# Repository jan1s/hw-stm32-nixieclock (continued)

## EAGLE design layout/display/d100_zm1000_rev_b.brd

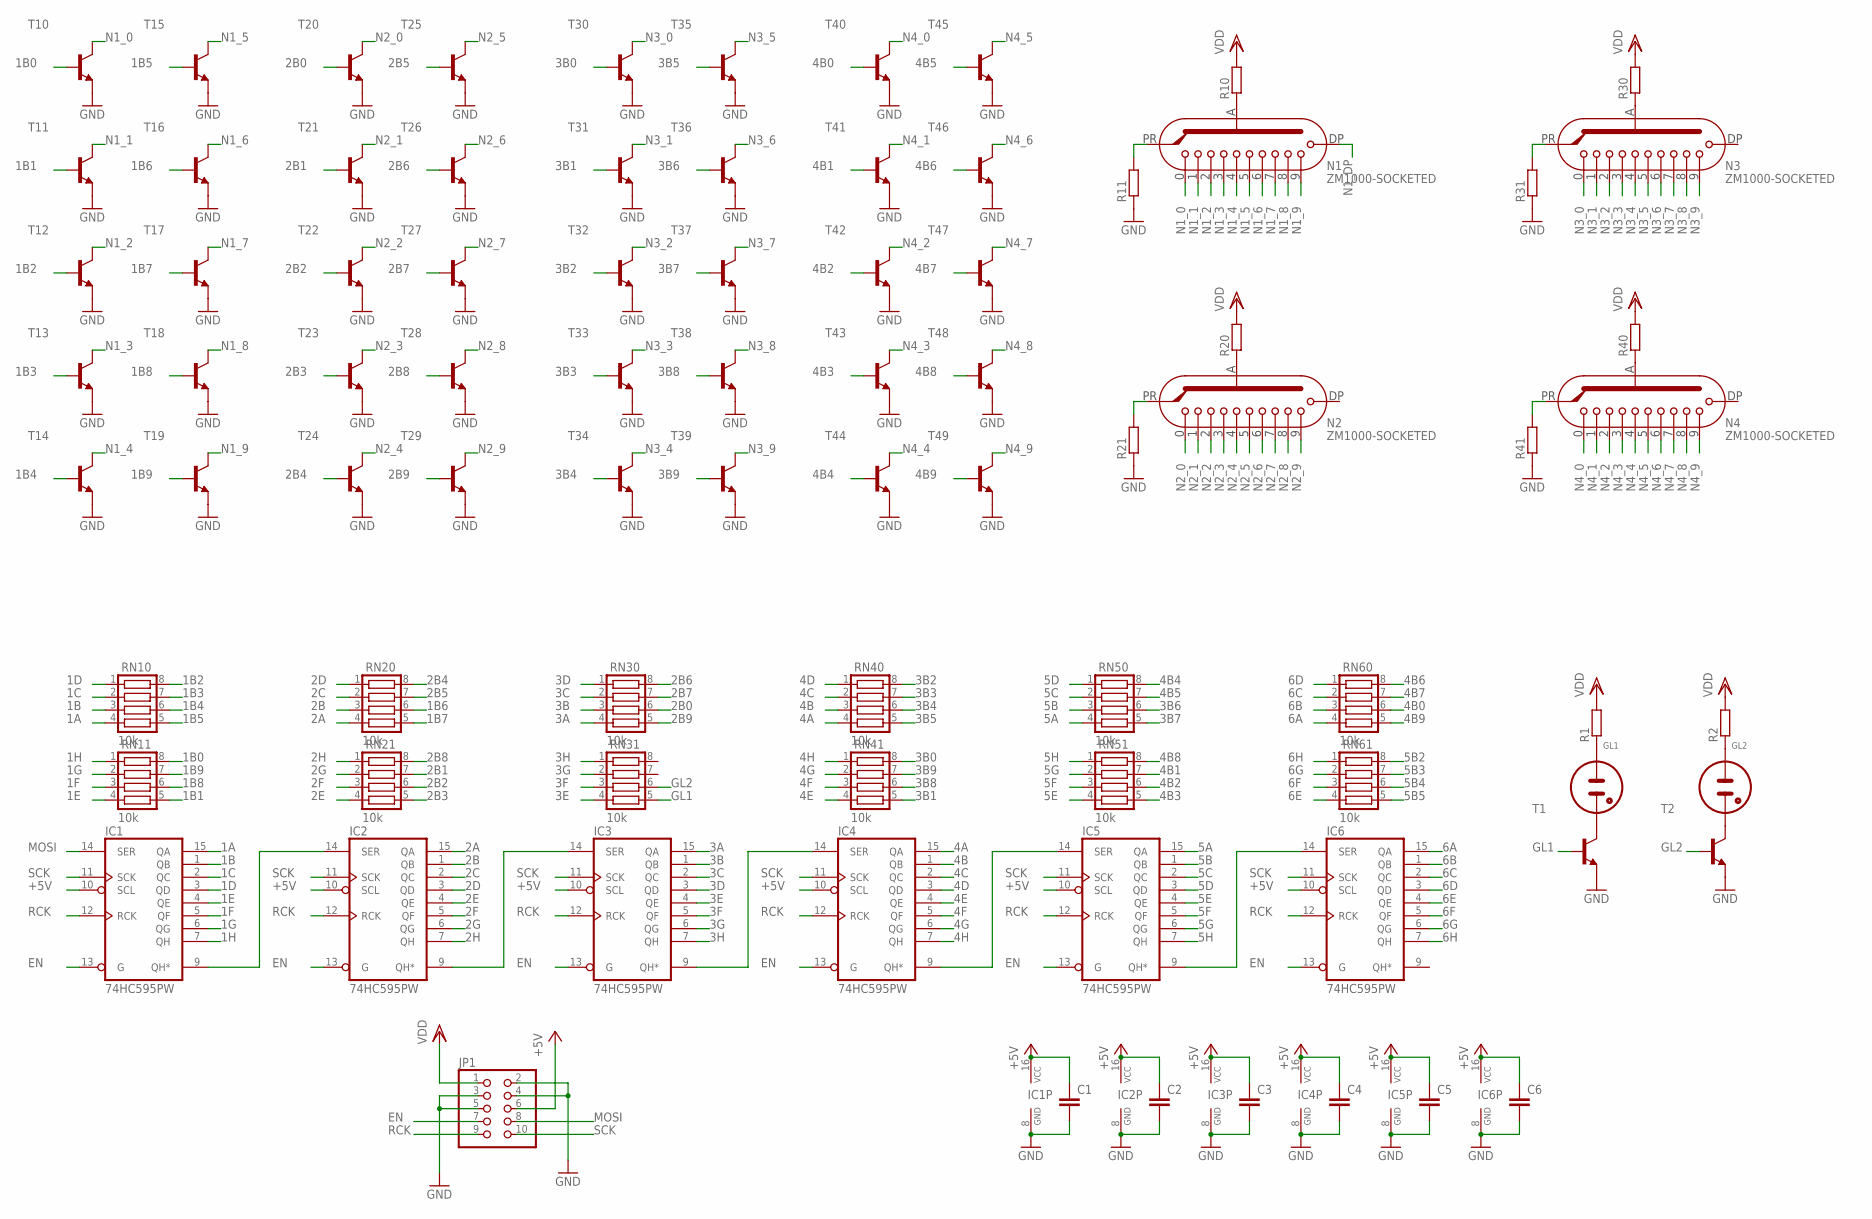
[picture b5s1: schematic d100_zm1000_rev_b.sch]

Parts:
C1, C2, C3, C4, C5, C6: C-EUC0603; C0603
GL1, GL2: NE2-NEON-BULB-DRILL
IC1, IC2, IC3, IC4, IC5, IC6: 74HC595PW; TSSOP16
JP1: PINHD-2X5_2.54-SMD; 2X05SMD
N1, N2, N3, N4: ZM1000-SOCKETED
R1, R2, R10, R11, R20, R21, R30, R31, R40, R41: R-EU_R0603; R0603
RN10, RN11, RN20, RN21, RN30, RN31, RN40, RN41, RN50, RN51, RN60, RN61: 10k; CTS742C083
T1, T2, T10, T11, T12, T13, T14, T15, T16, T17, T18, T19, T20, T21, T22, T23, T24, T25, T26, T27, T28, T29, T30, T31, T32, T33, T34, T35, T36, T37, T38, T39, T40, T41, T42, T43, T44, T45, T46, T47, T48, T49: SMBTA42; SOT23

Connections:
1A: IC1.15 (QA), RN10.4
1B: IC1.1 (QB), RN10.3
1B0: RN11.8, T10.1 (B)
1B1: RN11.5, T11.1 (B)
1B2: RN10.8, T12.1 (B)
1B3: RN10.7, T13.1 (B)
1B4: RN10.6, T14.1 (B)
1B5: RN10.5, T15.1 (B)
1B6: RN20.6, T16.1 (B)
1B7: RN20.5, T17.1 (B)
1B8: RN11.6, T18.1 (B)
1B9: RN11.7, T19.1 (B)
1C: IC1.2 (QC), RN10.2
1D: IC1.3 (QD), RN10.1
1E: IC1.4 (QE), RN11.4
1F: IC1.5 (QF), RN11.3
1G: IC1.6 (QG), RN11.2
1H: IC1.7 (QH), RN11.1
2A: IC2.15 (QA), RN20.4
2B: IC2.1 (QB), RN20.3
2B0: RN30.6, T20.1 (B)
2B1: RN21.7, T21.1 (B)
2B2: RN21.6, T22.1 (B)
2B3: RN21.5, T23.1 (B)
2B4: RN20.8, T24.1 (B)
2B5: RN20.7, T25.1 (B)
2B6: RN30.8, T26.1 (B)
2B7: RN30.7, T27.1 (B)
2B8: RN21.8, T28.1 (B)
2B9: RN30.5, T29.1 (B)
2C: IC2.2 (QC), RN20.2
2D: IC2.3 (QD), RN20.1
2E: IC2.4 (QE), RN21.4
2F: IC2.5 (QF), RN21.3
2G: IC2.6 (QG), RN21.2
2H: IC2.7 (QH), RN21.1
3A: IC3.15 (QA), RN30.4
3B: IC3.1 (QB), RN30.3
3B0: RN41.8, T30.1 (B)
3B1: RN41.5, T31.1 (B)
3B2: RN40.8, T32.1 (B)
3B3: RN40.7, T33.1 (B)
3B4: RN40.6, T34.1 (B)
3B5: RN40.5, T35.1 (B)
3B6: RN50.6, T36.1 (B)
3B7: RN50.5, T37.1 (B)
3B8: RN41.6, T38.1 (B)
3B9: RN41.7, T39.1 (B)
3C: IC3.2 (QC), RN30.2
3D: IC3.3 (QD), RN30.1
3E: IC3.4 (QE), RN31.4
3F: IC3.5 (QF), RN31.3
3G: IC3.6 (QG), RN31.2
3H: IC3.7 (QH), RN31.1
4A: IC4.15 (QA), RN40.4
4B: IC4.1 (QB), RN40.3
4B0: RN60.6, T40.1 (B)
4B1: RN51.7, T41.1 (B)
4B2: RN51.6, T42.1 (B)
4B3: RN51.5, T43.1 (B)
4B4: RN50.8, T44.1 (B)
4B5: RN50.7, T45.1 (B)
4B6: RN60.8, T46.1 (B)
4B7: RN60.7, T47.1 (B)
4B8: RN51.8, T48.1 (B)
4B9: RN60.5, T49.1 (B)
4C: IC4.2 (QC), RN40.2
4D: IC4.3 (QD), RN40.1
4E: IC4.4 (QE), RN41.4
4F: IC4.5 (QF), RN41.3
4G: IC4.6 (QG), RN41.2
4H: IC4.7 (QH), RN41.1
5A: IC5.15 (QA), RN50.4
5B: IC5.1 (QB), RN50.3
5B2: RN61.8
5B3: RN61.7
5B4: RN61.6
5B5: RN61.5
5C: IC5.2 (QC), RN50.2
5D: IC5.3 (QD), RN50.1
5E: IC5.4 (QE), RN51.4
5F: IC5.5 (QF), RN51.3
5G: IC5.6 (QG), RN51.2
5H: IC5.7 (QH), RN51.1
6A: IC6.15 (QA), RN60.4
6B: IC6.1 (QB), RN60.3
6C: IC6.2 (QC), RN60.2
6D: IC6.3 (QD), RN60.1
6E: IC6.4 (QE), RN61.4
6F: IC6.5 (QF), RN61.3
6G: IC6.6 (QG), RN61.2
6H: IC6.7 (QH), RN61.1
+5V: C1.1, C2.1, C3.1, C4.1, C5.1, C6.1, IC1.10 (SCL), IC1.16 (VCC), IC2.10 (SCL), IC2.16 (VCC), IC3.10 (SCL), IC3.16 (VCC), IC4.10 (SCL), IC4.16 (VCC), IC5.10 (SCL), IC5.16 (VCC), IC6.10 (SCL), IC6.16 (VCC), JP1.6
EN: IC1.13 (G), IC2.13 (G), IC3.13 (G), IC4.13 (G), IC5.13 (G), IC6.13 (G), JP1.7
GL1: RN31.5, T1.1 (B)
GL2: RN31.6, T2.1 (B)
GND: C1.2, C2.2, C3.2, C4.2, C5.2, C6.2, IC1.8 (GND), IC2.8 (GND), IC3.8 (GND), IC4.8 (GND), IC5.8 (GND), IC6.8 (GND), JP1.2, JP1.3, JP1.4, JP1.5, R11.1, R21.1, R31.1, R41.1, T1.2 (E), T2.2 (E), T10.2 (E), T11.2 (E), T12.2 (E), T13.2 (E), T14.2 (E), T15.2 (E), T16.2 (E), T17.2 (E), T18.2 (E), T19.2 (E), T20.2 (E), T21.2 (E), T22.2 (E), T23.2 (E), T24.2 (E), T25.2 (E), T26.2 (E), T27.2 (E), T28.2 (E), T29.2 (E), T30.2 (E), T31.2 (E), T32.2 (E), T33.2 (E), T34.2 (E), T35.2 (E), T36.2 (E), T37.2 (E), T38.2 (E), T39.2 (E), T40.2 (E), T41.2 (E), T42.2 (E), T43.2 (E), T44.2 (E), T45.2 (E), T46.2 (E), T47.2 (E), T48.2 (E), T49.2 (E)
MOSI: IC1.14 (SER), JP1.8
N1_0: N1.K0 (0), T10.3 (C)
N1_1: N1.K1 (1), T11.3 (C)
N1_2: N1.K2 (2), T12.3 (C)
N1_3: N1.K3 (3), T13.3 (C)
N1_4: N1.K4 (4), T14.3 (C)
N1_5: N1.K5 (5), T15.3 (C)
N1_6: N1.K6 (6), T16.3 (C)
N1_7: N1.K7 (7), T17.3 (C)
N1_8: N1.K8 (8), T18.3 (C)
N1_9: N1.K9 (9), T19.3 (C)
N1_DP: N1.KDP (DP)
N1_PR: N1.PR, R11.2
N2_0: N2.K0 (0), T20.3 (C)
N2_1: N2.K1 (1), T21.3 (C)
N2_2: N2.K2 (2), T22.3 (C)
N2_3: N2.K3 (3), T23.3 (C)
N2_4: N2.K4 (4), T24.3 (C)
N2_5: N2.K5 (5), T25.3 (C)
N2_6: N2.K6 (6), T26.3 (C)
N2_7: N2.K7 (7), T27.3 (C)
N2_8: N2.K8 (8), T28.3 (C)
N2_9: N2.K9 (9), T29.3 (C)
N3_0: N3.K0 (0), T30.3 (C)
N3_1: N3.K1 (1), T31.3 (C)
N3_2: N3.K2 (2), T32.3 (C)
N3_3: N3.K3 (3), T33.3 (C)
N3_4: N3.K4 (4), T34.3 (C)
N3_5: N3.K5 (5), T35.3 (C)
N3_6: N3.K6 (6), T36.3 (C)
N3_7: N3.K7 (7), T37.3 (C)
N3_8: N3.K8 (8), T38.3 (C)
N3_9: N3.K9 (9), T39.3 (C)
N4_0: N4.K0 (0), T40.3 (C)
N4_1: N4.K1 (1), T41.3 (C)
N4_2: N4.K2 (2), T42.3 (C)
N4_3: N4.K3 (3), T43.3 (C)
N4_4: N4.K4 (4), T44.3 (C)
N4_5: N4.K5 (5), T45.3 (C)
N4_6: N4.K6 (6), T46.3 (C)
N4_7: N4.K7 (7), T47.3 (C)
N4_8: N4.K8 (8), T48.3 (C)
N4_9: N4.K9 (9), T49.3 (C)
unnamed: GL2.1 (A), R2.1
unnamed: N1.A1 (A), N1.A2 (A), R10.1
unnamed: GL2.2 (A1), T2.3 (C)
unnamed: GL1.2 (A1), T1.3 (C)
unnamed: N2.A1 (A), N2.A2 (A), R20.1
unnamed: IC1.9 (QH*), IC2.14 (SER)
unnamed: IC2.9 (QH*), IC3.14 (SER)
unnamed: IC3.9 (QH*), IC4.14 (SER)
unnamed: N3.A1 (A), N3.A2 (A), R30.1
unnamed: N4.A1 (A), N4.A2 (A), R40.1
unnamed: IC4.9 (QH*), IC5.14 (SER)
unnamed: IC5.9 (QH*), IC6.14 (SER)
unnamed: GL1.1 (A), R1.1
unnamed: N3.PR, R31.2
unnamed: N2.PR, R21.2
unnamed: N4.PR, R41.2
RCK: IC1.12 (RCK), IC2.12 (RCK), IC3.12 (RCK), IC4.12 (RCK), IC5.12 (RCK), IC6.12 (RCK), JP1.9
SCK: IC1.11 (SCK), IC2.11 (SCK), IC3.11 (SCK), IC4.11 (SCK), IC5.11 (SCK), IC6.11 (SCK), JP1.10
VDD: JP1.1, R1.2, R2.2, R10.2, R20.2, R30.2, R40.2

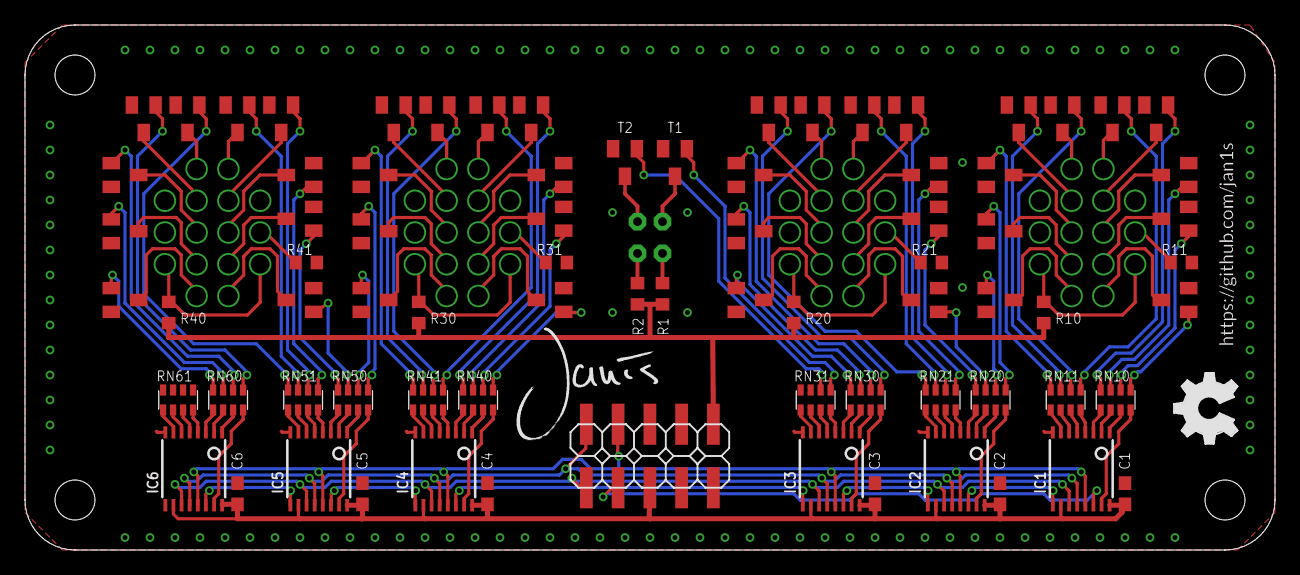
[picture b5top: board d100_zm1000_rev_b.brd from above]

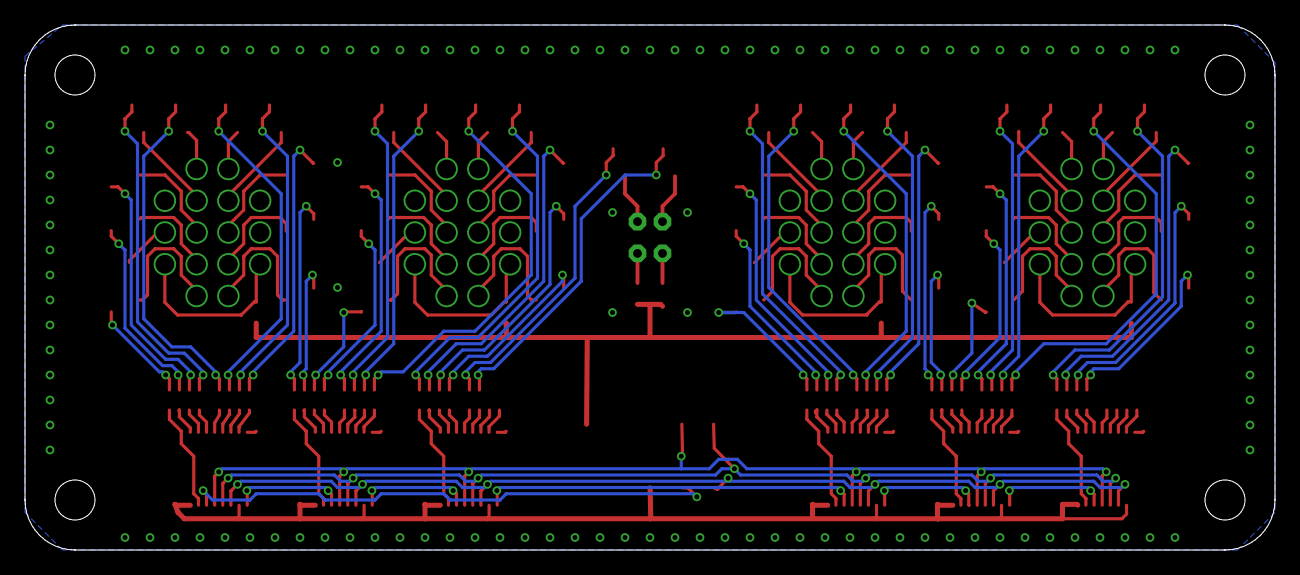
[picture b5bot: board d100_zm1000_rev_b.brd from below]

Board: 2 copper layers, 100.0 x 42.0 mm, 86 parts (6 on the bottom side), 154 nets.

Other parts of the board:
U$1: GITHUB/JAN1S
U$2: JANIS_10MM
U$3: OSHW_FILLX200_NOTEXT

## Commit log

2015-11-17 Added control pcb render
2015-11-17 Added case
2015-11-17 Added BT timesource
2015-12-08 Added BOM list
2015-12-08 Fixed values
2015-12-30 Fixes in case
2015-12-31 Fixed display bug
2016-01-02 Changed structure, added HM-11
2016-01-03 Changed structure, added c150 and c200
2016-01-03 C100 production ready
2016-01-03 Finished c150 rev a
2016-01-03 Added control pcb readme
2016-01-03 Added display readme
2016-01-03 Fixed readme
2016-01-13 Added detail of c100, d100 rev a bodges
2016-01-13 Revert "Added detail of c100, d100 rev a bodges"
    This reverts commit f08b87db82e6815f0eeb61e454d55ffe807eec73.
2016-01-13 Added detail of rev a bodges
2016-01-14 Added Readme
2016-01-17 Fixed naming
2016-12-18 Added ESP-12
2016-12-18 Added final c200 production files
2016-12-29 Added Wifi Module
2017-02-11 Fixed RX/TX
2017-09-01 Added updated wifi source
2017-10-22 Added rev. B, Fixed connector distance...
2017-11-01 Added rev. B of large clock layouts
2018-01-07 Added new control board versions and TRS adapter
2018-08-03 Added new c150 board
2018-08-03 C200 missing..
2018-08-03 Added HV module
2020-02-05 Added c100_rev_e
